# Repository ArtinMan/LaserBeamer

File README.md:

# LaserBeamer
'''My build: IMR18650 3.7V 1500mAh cell → USB-C charging via TP4056 (~1A charge rate) → DW01A + FS8205A protection → latching power switch → AP2112K-3.3 regulator → 532nm 5mW laser diode module. Green LED shows charging status.'''

#Few Concepts to know:
'''Schematic vs. PCB. The schematic is a logical diagram — what connects to what, regardless of physical size or position. The PCB is the physical board. Schematic always comes first.

Nets. A "net" is a name for a group of pins that are all the same electrical point. Same net name = connected, even without a drawn line between them.

Why so many capacitors. Small ceramic capacitors near a chip's power pins smooth out sudden current draw changes. Every IC here gets one nearby its power pin. Just place them close to the chip they support.

No-connect flags. Some chip pins are intentionally left unused in a given design. KiCad's Electrical Rules Checker (ERC) doesn't know that's intentional unless you tell it — you do that by placing a small "X" marker (a no-connect flag) directly on that pin. Skipping this doesn't break the circuit, but it clutters your ERC report with false warnings, making it harder to spot real problems.

Reference designators. U1, R3, J4, etc. — letter = part type, number = which one. Don't worry about matching numbers exactly to this guide; KiCad's Annotate step cleans these up automatically at the end.'''

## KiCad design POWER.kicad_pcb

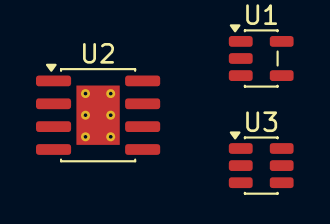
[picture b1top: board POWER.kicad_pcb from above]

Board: 2 copper layers, 3 parts (0 on the bottom side), 3 nets, no tracks yet.

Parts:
U1: AP2112K-3.3; SOT-23-5
U2: TP4056-42-ESOP8; SOIC-8-1EP_3.9x4.9mm_P1.27mm_EP2.41x3.3mm_ThermalVias
U3: DW01A; SOT-23-6

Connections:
/CELL+: U2.5 (BAT), U3.5 (VCC)
/VBAT_SW: U1.1 (VIN), U1.3 (EN), U1.5 (VOUT)
GND: U1.2 (GND), U2.1 (TEMP), U2.3 (GND), U2.8 (CE), U2.9 (EPAD), U3.6 (GND)
